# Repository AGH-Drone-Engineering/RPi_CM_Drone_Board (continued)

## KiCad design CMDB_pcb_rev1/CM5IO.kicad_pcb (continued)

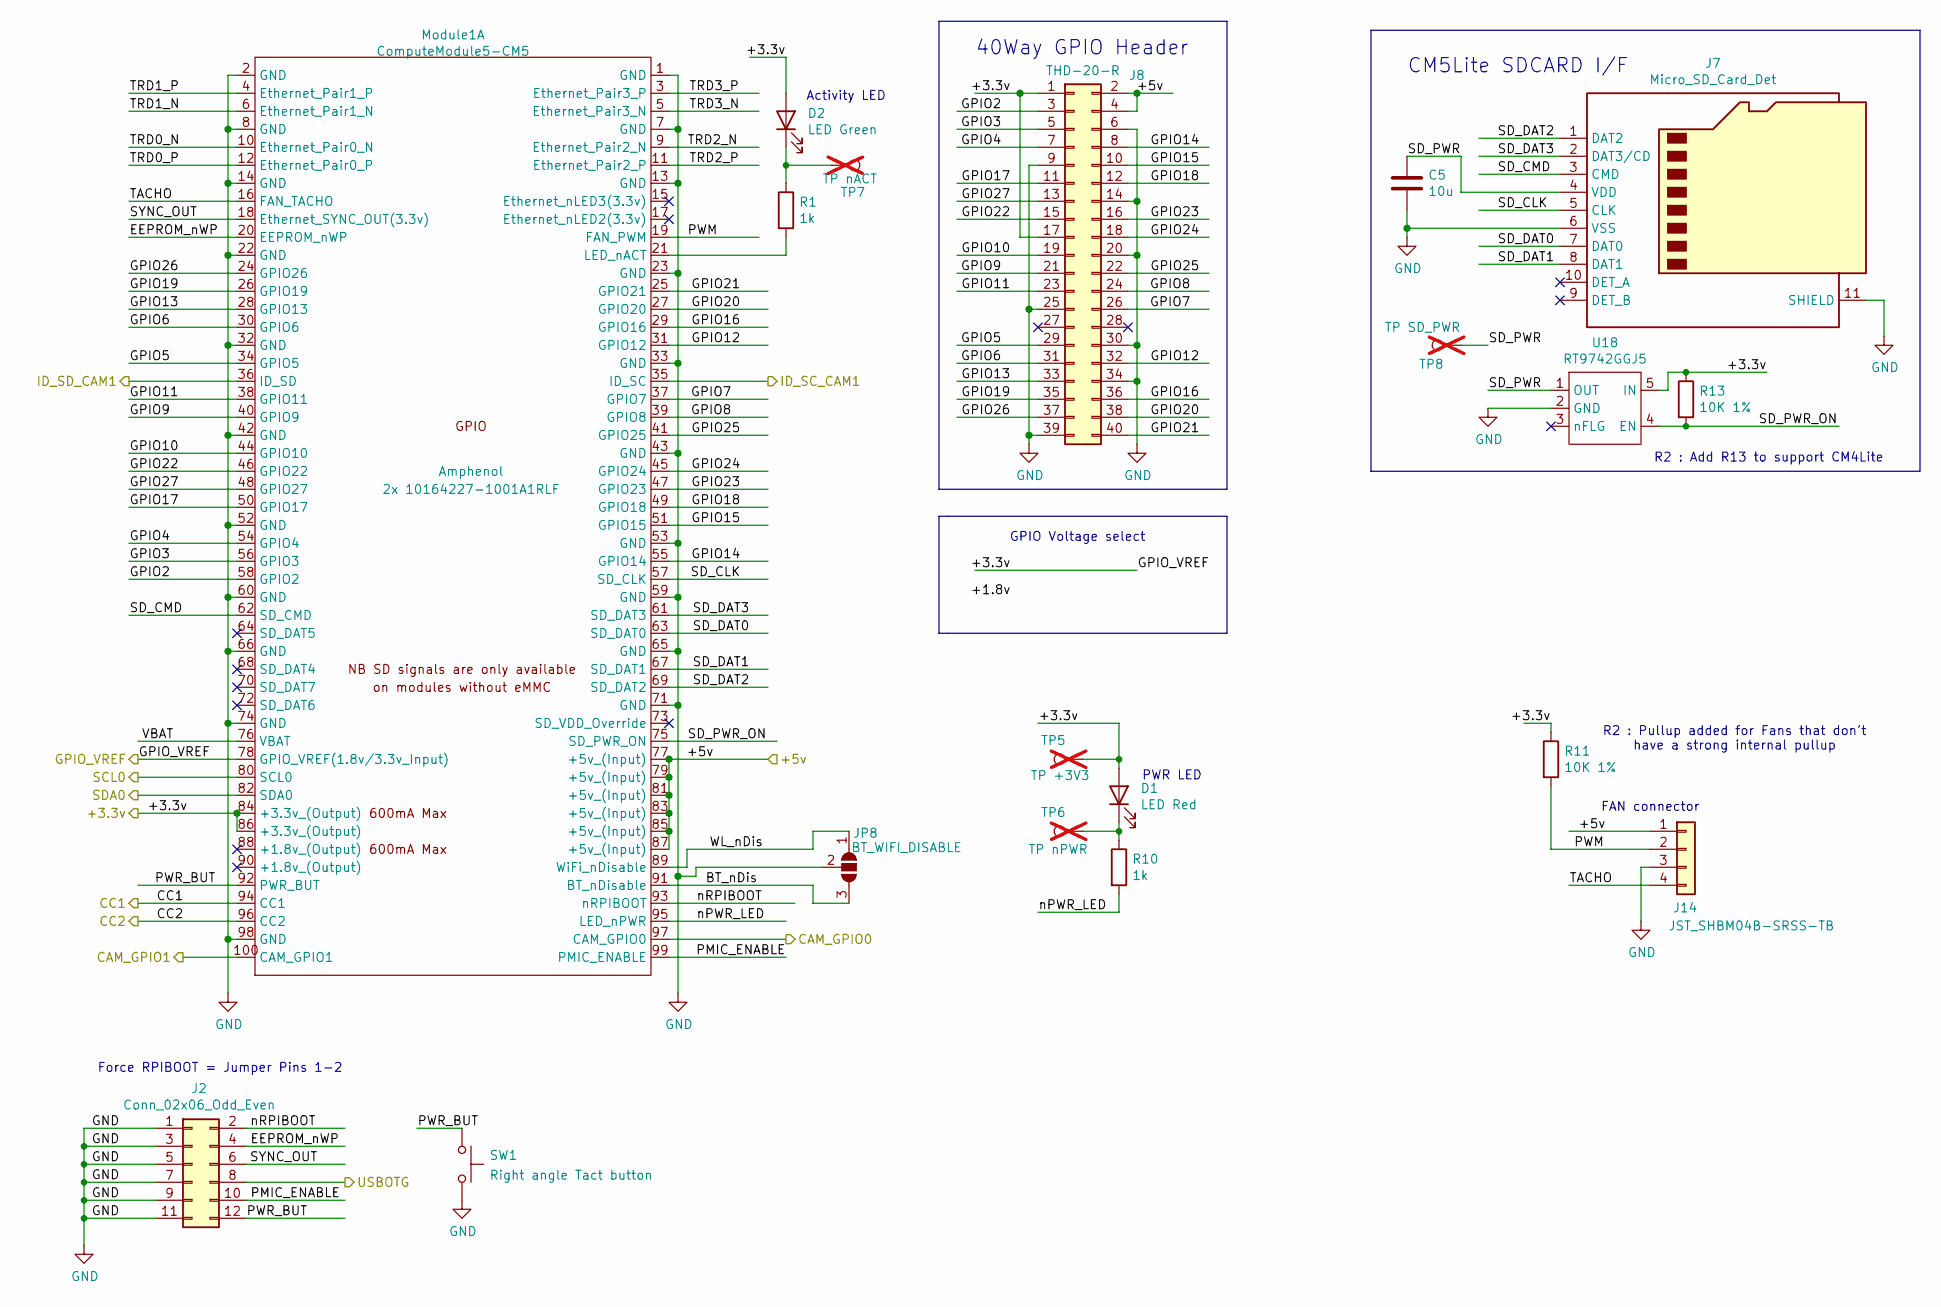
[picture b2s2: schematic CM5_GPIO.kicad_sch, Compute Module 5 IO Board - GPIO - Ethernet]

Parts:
C5: 10u; C_0805_2012Metric; Part Description 10uF 10% 10V Ceramic Capacitor X7R 0805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
D1: LED Red; LED_0603_1608Metric; Part Description Red 620nm LED Indication - Discrete 2.2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
D2: LED Green; LED_0603_1608Metric; Part Description Green 572nm LED Indication - Discrete 2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
J2: Conn_02x06_Odd_Even; PinHeader_2x06_P2.00mm_Vertical; Part Description PinHeader_2x06_P2.54mm_Vertical
J7: Micro_SD_Card_Det; SDCARD_MOLEX_503398-1892; Part Description 9 (8 + 1) Position Card Connector micro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
J8: THD-20-R; PinHeader_2x20_P2.54mm_Vertical; Part Description PinHeader_2x20_P2.54mm_Vertical
J14: JST_SHBM04B-SRSS-TB; JST_SH_BM04B-SRSS-TB_1x04-1MP_P1.00mm_Vertical; Part Description 4 pin vertical 1mm pitch connector
JP8: BT_WIFI_DISABLE; SolderJumper-3_P2.0mm_Open_TrianglePad1.0x1.5mm
Module1: ComputeModule5-CM5; Raspberry-Pi-5-Compute-Module; Part Description 100 Position Connector Receptacle, Cent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
R1, R10: 1k; R_0402_1005Metric; Part Description Resistor 1K M1005 1% 63mW
R11, R13: 10K 1%; R_0402_1005Metric; Part Description Resistor 10K M1005 1% 63mW
SW1: Right angle Tact button; SW_Push_1P1T_NO_CK_KMR2
TP5: TP +3V3; TestPoint_Pad_2.0x2.0mm; Part Description Test point; not fitted
TP6: TP nPWR; TestPoint_Pad_2.0x2.0mm; Part Description Test point; not fitted
TP7: TP nACT; TestPoint_Pad_2.0x2.0mm; Part Description Test point; not fitted
TP8: TP SD_PWR; TestPoint_Pad_2.0x2.0mm; Part Description Test point; not fitted
U18: RT9742GGJ5; SOT-23-5; Part Description Power Switch/Driver 1:1 N-Channel 1A TS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

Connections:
/+3.3v: D1.2 (A), D2.2 (A), J8.1, J8.17, Module1.78 (GPIO_VREF(1.8v/3.3v_Input)), Module1.84 (+3.3v_(Output)), Module1.86 (+3.3v_(Output)), R11.1, R13.1, TP5.1, U18.5 (IN); also elsewhere on the board
/+5v: J8.2, J8.4, J14.1, Module1.77 (+5v_(Input)), Module1.79 (+5v_(Input)), Module1.81 (+5v_(Input)), Module1.83 (+5v_(Input)), Module1.85 (+5v_(Input)), Module1.87 (+5v_(Input)); also elsewhere on the board
/CC1: Module1.94 (CC1); also elsewhere on the board
/CC2: Module1.96 (CC2); also elsewhere on the board
/CM5_GPIO ( Ethernet, GPIO, SDCARD)/BT_nDis: JP8.3 (B), Module1.91 (BT_nDisable)
/CM5_GPIO ( Ethernet, GPIO, SDCARD)/CAM_GPIO0: Module1.97 (CAM_GPIO0); also elsewhere on the board
/CM5_GPIO ( Ethernet, GPIO, SDCARD)/CAM_GPIO1: Module1.100 (CAM_GPIO1); also elsewhere on the board
/CM5_GPIO ( Ethernet, GPIO, SDCARD)/EEPROM_nWP: J2.4, Module1.20 (EEPROM_nWP)
/CM5_GPIO ( Ethernet, GPIO, SDCARD)/GPIO2: J8.3, Module1.58 (GPIO2)
/CM5_GPIO ( Ethernet, GPIO, SDCARD)/GPIO3: J8.5, Module1.56 (GPIO3)
/CM5_GPIO ( Ethernet, GPIO, SDCARD)/GPIO4: J8.7, Module1.54 (GPIO4)
/CM5_GPIO ( Ethernet, GPIO, SDCARD)/GPIO5: J8.29, Module1.34 (GPIO5)
/CM5_GPIO ( Ethernet, GPIO, SDCARD)/GPIO6: J8.31, Module1.30 (GPIO6)
/CM5_GPIO ( Ethernet, GPIO, SDCARD)/GPIO7: J8.26, Module1.37 (GPIO7)
/CM5_GPIO ( Ethernet, GPIO, SDCARD)/GPIO8: J8.24, Module1.39 (GPIO8)
/CM5_GPIO ( Ethernet, GPIO, SDCARD)/GPIO9: J8.21, Module1.40 (GPIO9)
/CM5_GPIO ( Ethernet, GPIO, SDCARD)/GPIO10: J8.19, Module1.44 (GPIO10)
/CM5_GPIO ( Ethernet, GPIO, SDCARD)/GPIO11: J8.23, Module1.38 (GPIO11)
/CM5_GPIO ( Ethernet, GPIO, SDCARD)/GPIO12: J8.32, Module1.31 (GPIO12)
/CM5_GPIO ( Ethernet, GPIO, SDCARD)/GPIO13: J8.33, Module1.28 (GPIO13)
/CM5_GPIO ( Ethernet, GPIO, SDCARD)/GPIO14: J8.8, Module1.55 (GPIO14)
/CM5_GPIO ( Ethernet, GPIO, SDCARD)/GPIO15: J8.10, Module1.51 (GPIO15)
/CM5_GPIO ( Ethernet, GPIO, SDCARD)/GPIO16: J8.36, Module1.29 (GPIO16)
/CM5_GPIO ( Ethernet, GPIO, SDCARD)/GPIO17: J8.11, Module1.50 (GPIO17)
/CM5_GPIO ( Ethernet, GPIO, SDCARD)/GPIO18: J8.12, Module1.49 (GPIO18)
/CM5_GPIO ( Ethernet, GPIO, SDCARD)/GPIO19: J8.35, Module1.26 (GPIO19)
/CM5_GPIO ( Ethernet, GPIO, SDCARD)/GPIO20: J8.38, Module1.27 (GPIO20)
/CM5_GPIO ( Ethernet, GPIO, SDCARD)/GPIO21: J8.40, Module1.25 (GPIO21)
/CM5_GPIO ( Ethernet, GPIO, SDCARD)/GPIO22: J8.15, Module1.46 (GPIO22)
/CM5_GPIO ( Ethernet, GPIO, SDCARD)/GPIO23: J8.16, Module1.47 (GPIO23)
/CM5_GPIO ( Ethernet, GPIO, SDCARD)/GPIO24: J8.18, Module1.45 (GPIO24)
/CM5_GPIO ( Ethernet, GPIO, SDCARD)/GPIO25: J8.22, Module1.41 (GPIO25)
/CM5_GPIO ( Ethernet, GPIO, SDCARD)/GPIO26: J8.37, Module1.24 (GPIO26)
/CM5_GPIO ( Ethernet, GPIO, SDCARD)/GPIO27: J8.13, Module1.48 (GPIO27)
/CM5_GPIO ( Ethernet, GPIO, SDCARD)/PMIC_ENABLE: J2.10, Module1.99 (PMIC_ENABLE)
/CM5_GPIO ( Ethernet, GPIO, SDCARD)/PWM: J14.2, Module1.19 (FAN_PWM), R11.2
/CM5_GPIO ( Ethernet, GPIO, SDCARD)/PWR_BUT: J2.12, Module1.92 (PWR_BUT), SW1.1
/CM5_GPIO ( Ethernet, GPIO, SDCARD)/SD_CLK: J7.5 (CLK), Module1.57 (SD_CLK)
/CM5_GPIO ( Ethernet, GPIO, SDCARD)/SD_CMD: J7.3 (CMD), Module1.62 (SD_CMD)
/CM5_GPIO ( Ethernet, GPIO, SDCARD)/SD_DAT0: J7.7 (DAT0), Module1.63 (SD_DAT0)
/CM5_GPIO ( Ethernet, GPIO, SDCARD)/SD_DAT1: J7.8 (DAT1), Module1.67 (SD_DAT1)
/CM5_GPIO ( Ethernet, GPIO, SDCARD)/SD_DAT2: J7.1 (DAT2), Module1.69 (SD_DAT2)
/CM5_GPIO ( Ethernet, GPIO, SDCARD)/SD_DAT3: J7.2 (DAT3/CD), Module1.61 (SD_DAT3)
/CM5_GPIO ( Ethernet, GPIO, SDCARD)/SD_PWR: C5.1, J7.4 (VDD), TP8.1, U18.1 (OUT)
/CM5_GPIO ( Ethernet, GPIO, SDCARD)/SD_PWR_ON: Module1.75 (SD_PWR_ON), R13.2, U18.4 (EN)
/CM5_GPIO ( Ethernet, GPIO, SDCARD)/SYNC_OUT: J2.6, Module1.18 (Ethernet_SYNC_OUT(3.3v))
/CM5_GPIO ( Ethernet, GPIO, SDCARD)/TACHO: J14.4, Module1.16 (FAN_TACHO)
/CM5_GPIO ( Ethernet, GPIO, SDCARD)/TRD0_N: Module1.10 (Ethernet_Pair0_N)
/CM5_GPIO ( Ethernet, GPIO, SDCARD)/TRD0_P: Module1.12 (Ethernet_Pair0_P)
/CM5_GPIO ( Ethernet, GPIO, SDCARD)/TRD1_N: Module1.6 (Ethernet_Pair1_N)
/CM5_GPIO ( Ethernet, GPIO, SDCARD)/TRD1_P: Module1.4 (Ethernet_Pair1_P)
/CM5_GPIO ( Ethernet, GPIO, SDCARD)/TRD2_N: Module1.9 (Ethernet_Pair2_N)
/CM5_GPIO ( Ethernet, GPIO, SDCARD)/TRD2_P: Module1.11 (Ethernet_Pair2_P)
/CM5_GPIO ( Ethernet, GPIO, SDCARD)/TRD3_N: Module1.5 (Ethernet_Pair3_N)
/CM5_GPIO ( Ethernet, GPIO, SDCARD)/TRD3_P: Module1.3 (Ethernet_Pair3_P)
/CM5_GPIO ( Ethernet, GPIO, SDCARD)/USBOTG: J2.8; also elsewhere on the board
/CM5_GPIO ( Ethernet, GPIO, SDCARD)/VBAT: Module1.76 (VBAT)
/CM5_GPIO ( Ethernet, GPIO, SDCARD)/WL_nDis: JP8.1 (A), Module1.89 (WiFi_nDisable)
/CM5_GPIO ( Ethernet, GPIO, SDCARD)/nPWR_LED: Module1.95 (LED_nPWR), R10.2
/CM5_GPIO ( Ethernet, GPIO, SDCARD)/nRPIBOOT: J2.2, Module1.93 (nRPIBOOT)
/CM5_HighSpeed/SCL0: Module1.80 (SCL0); also elsewhere on the board
/CM5_HighSpeed/SCL1: Module1.35 (ID_SC); also elsewhere on the board
/CM5_HighSpeed/SDA0: Module1.82 (SDA0); also elsewhere on the board
/CM5_HighSpeed/SDA1: Module1.36 (ID_SD); also elsewhere on the board
GND: C5.2, J2.1, J2.3, J2.5, J2.7, J2.9, J2.11, J7.6 (VSS), J7.11 (SHIELD), J8.6, J8.9, J8.14, J8.20, J8.25, J8.30, J8.34, J8.39, J14.3, JP8.2 (C), Module1.1 (GND), Module1.2 (GND), Module1.7 (GND), Module1.8 (GND), Module1.13 (GND), Module1.14 (GND), Module1.22 (GND), Module1.23 (GND), Module1.32 (GND), Module1.33 (GND), Module1.42 (GND), Module1.43 (GND), Module1.52 (GND), Module1.53 (GND), Module1.59 (GND), Module1.60 (GND), Module1.65 (GND), Module1.66 (GND), Module1.71 (GND), Module1.74 (GND), Module1.98 (GND), SW1.2, U18.2 (GND); also elsewhere on the board
unnamed: D1.1 (K), R10.1, TP6.1
unnamed: D2.1 (K), R1.1, TP7.1
unnamed: Module1.21 (LED_nACT), R1.2

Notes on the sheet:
40Way GPIO Header
R2 : Pullup added for Fans that don't have a strong internal pullup
Activity LED
R2 : Add R13 to support CM4Lite
GPIO Voltage select
Force RPIBOOT = Jumper Pins 1-2
PWR LED
FAN connector
CM5Lite SDCARD I/F

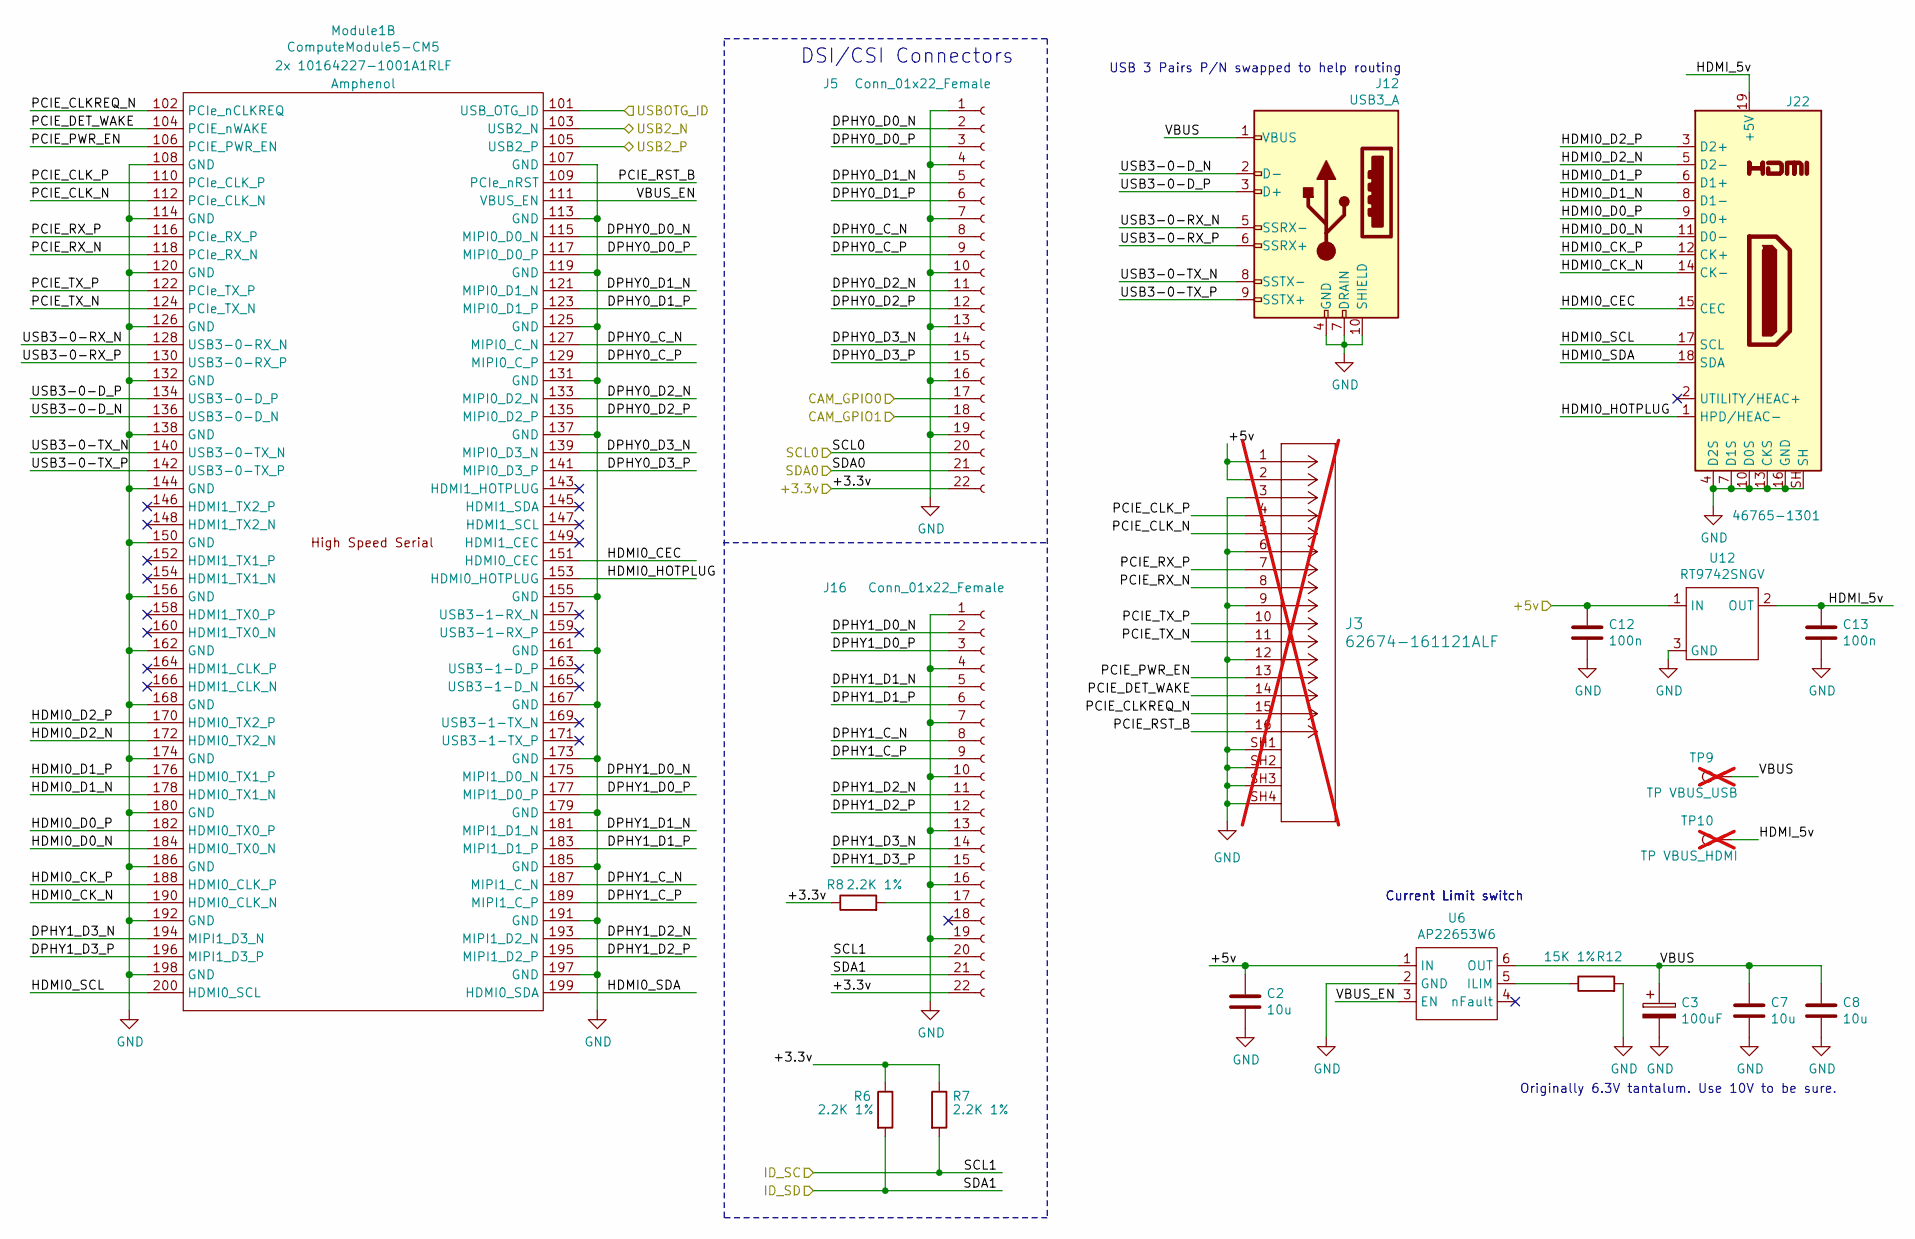
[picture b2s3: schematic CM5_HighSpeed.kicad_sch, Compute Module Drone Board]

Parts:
C2, C7, C8: 10u; C_0805_2012Metric; Part Description 10uF 10% 10V Ceramic Capacitor X7R 0805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
C3: 100uF; CP_EIA-7343-31_Kemet-D; Part Description Capacitor, SP-Cap, 100u, 6.3V, 15mR ESR
C12, C13: 100n; C_0402_1005Metric; Part Description 0.1uF 10% 16V Ceramic Capacitor X7R 040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
J3: 62674-161121ALF; CON16_1X16_DUT_58XF_GLE; not fitted
J5, J16: Conn_01x22_Female; Hirose_FH12-22S-0.5SH_1x22-1MP_P0.50mm_Horizontal; Part Description 22 Position FFC, FPC Connector Contacts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
J12: USB3_A; USB3_A_Molex_48393-001; Part Description USB 3.0 A connector
J22: 46765-1301; CONN_467651301_MOL; Part Description 0.40mm Pitch Micro HDMI Connector, Righ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
Module1: ComputeModule5-CM5; Raspberry-Pi-5-Compute-Module; Part Description 100 Position Connector Receptacle, Cent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
R6, R7, R8: 2.2K 1%; R_0402_1005Metric; Part Description Resistor 2.2K M1005 1% 63mW
R12: 15K 1%; R_0402_1005Metric; Part Description Resistor 15K M1005 1% 63mW
TP9: TP VBUS_USB; TestPoint_Pad_2.0x2.0mm; Part Description Test point; not fitted
TP10: TP VBUS_HDMI; TestPoint_Pad_2.0x2.0mm; Part Description Test point; not fitted
U6: AP22653W6; SOT-23-6; Part Description Power Switch/Driver 1:1 P-Channel 2.1A 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
U12: RT9742SNGV; TSOT-23_HandSoldering; Part Description Power Switch/Driver 1:1 N-Channel 500mA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

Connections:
/+3.3v: J5.22, J16.22, R6.1, R7.1, R8.1; also elsewhere on the board
/+5v: C2.1, C12.1, J3.1, J3.2, U6.1 (IN), U12.1 (IN); also elsewhere on the board
/CM5_GPIO ( Ethernet, GPIO, SDCARD)/CAM_GPIO0: J5.17; also elsewhere on the board
/CM5_GPIO ( Ethernet, GPIO, SDCARD)/CAM_GPIO1: J5.18; also elsewhere on the board
/CM5_GPIO ( Ethernet, GPIO, SDCARD)/USBOTG: Module1.101 (USB_OTG_ID); also elsewhere on the board
/CM5_HighSpeed/DPHY0_C_N: J5.8, Module1.127 (MIPI0_C_N)
/CM5_HighSpeed/DPHY0_C_P: J5.9, Module1.129 (MIPI0_C_P)
/CM5_HighSpeed/DPHY0_D0_N: J5.2, Module1.115 (MIPI0_D0_N)
/CM5_HighSpeed/DPHY0_D0_P: J5.3, Module1.117 (MIPI0_D0_P)
/CM5_HighSpeed/DPHY0_D1_N: J5.5, Module1.121 (MIPI0_D1_N)
/CM5_HighSpeed/DPHY0_D1_P: J5.6, Module1.123 (MIPI0_D1_P)
/CM5_HighSpeed/DPHY0_D2_N: J5.11, Module1.133 (MIPI0_D2_N)
/CM5_HighSpeed/DPHY0_D2_P: J5.12, Module1.135 (MIPI0_D2_P)
/CM5_HighSpeed/DPHY0_D3_N: J5.14, Module1.139 (MIPI0_D3_N)
/CM5_HighSpeed/DPHY0_D3_P: J5.15, Module1.141 (MIPI0_D3_P)
/CM5_HighSpeed/DPHY1_C_N: J16.8, Module1.187 (MIPI1_C_N)
/CM5_HighSpeed/DPHY1_C_P: J16.9, Module1.189 (MIPI1_C_P)
/CM5_HighSpeed/DPHY1_D0_N: J16.2, Module1.175 (MIPI1_D0_N)
/CM5_HighSpeed/DPHY1_D0_P: J16.3, Module1.177 (MIPI1_D0_P)
/CM5_HighSpeed/DPHY1_D1_N: J16.5, Module1.181 (MIPI1_D1_N)
/CM5_HighSpeed/DPHY1_D1_P: J16.6, Module1.183 (MIPI1_D1_P)
/CM5_HighSpeed/DPHY1_D2_N: J16.11, Module1.193 (MIPI1_D2_N)
/CM5_HighSpeed/DPHY1_D2_P: J16.12, Module1.195 (MIPI1_D2_P)
/CM5_HighSpeed/DPHY1_D3_N: J16.14, Module1.194 (MIPI1_D3_N)
/CM5_HighSpeed/DPHY1_D3_P: J16.15, Module1.196 (MIPI1_D3_P)
/CM5_HighSpeed/HDMI0_CEC: J22.15 (CEC), Module1.151 (HDMI0_CEC)
/CM5_HighSpeed/HDMI0_CK_N: J22.14 (CK-), Module1.190 (HDMI0_CLK_N)
/CM5_HighSpeed/HDMI0_CK_P: J22.12 (CK+), Module1.188 (HDMI0_CLK_P)
/CM5_HighSpeed/HDMI0_D0_N: J22.11 (D0-), Module1.184 (HDMI0_TX0_N)
/CM5_HighSpeed/HDMI0_D0_P: J22.9 (D0+), Module1.182 (HDMI0_TX0_P)
/CM5_HighSpeed/HDMI0_D1_N: J22.8 (D1-), Module1.178 (HDMI0_TX1_N)
/CM5_HighSpeed/HDMI0_D1_P: J22.6 (D1+), Module1.176 (HDMI0_TX1_P)
/CM5_HighSpeed/HDMI0_D2_N: J22.5 (D2-), Module1.172 (HDMI0_TX2_N)
/CM5_HighSpeed/HDMI0_D2_P: J22.3 (D2+), Module1.170 (HDMI0_TX2_P)
/CM5_HighSpeed/HDMI0_HOTPLUG: J22.1 (HPD/HEAC-), Module1.153 (HDMI0_HOTPLUG)
/CM5_HighSpeed/HDMI0_SCL: J22.17 (SCL), Module1.200 (HDMI0_SCL)
/CM5_HighSpeed/HDMI0_SDA: J22.18 (SDA), Module1.199 (HDMI0_SDA)
/CM5_HighSpeed/HDMI_5v: C13.1, J22.19 (+5V), TP10.1, U12.2 (OUT)
/CM5_HighSpeed/PCIE_CLKREQ_N: J3.15, Module1.102 (PCIe_nCLKREQ)
/CM5_HighSpeed/PCIE_CLK_N: J3.5, Module1.112 (PCIe_CLK_N)
/CM5_HighSpeed/PCIE_CLK_P: J3.4, Module1.110 (PCIe_CLK_P)
/CM5_HighSpeed/PCIE_DET_WAKE: J3.14, Module1.104 (PCIE_nWAKE)
/CM5_HighSpeed/PCIE_PWR_EN: J3.13, Module1.106 (PCIE_PWR_EN)
/CM5_HighSpeed/PCIE_RST_B: J3.16, Module1.109 (PCIe_nRST)
/CM5_HighSpeed/PCIE_RX_N: J3.8, Module1.118 (PCIe_RX_N)
/CM5_HighSpeed/PCIE_RX_P: J3.7, Module1.116 (PCIe_RX_P)
/CM5_HighSpeed/PCIE_TX_N: J3.11, Module1.124 (PCIe_TX_N)
/CM5_HighSpeed/PCIE_TX_P: J3.10, Module1.122 (PCIe_TX_P)
/CM5_HighSpeed/SCL0: J5.20; also elsewhere on the board
/CM5_HighSpeed/SCL1: J16.20, R7.2; also elsewhere on the board
/CM5_HighSpeed/SDA0: J5.21; also elsewhere on the board
/CM5_HighSpeed/SDA1: J16.21, R6.2; also elsewhere on the board
/CM5_HighSpeed/USB3-0-D_N: J12.2 (D-), Module1.136 (USB3-0-D_N)
/CM5_HighSpeed/USB3-0-D_P: J12.3 (D+), Module1.134 (USB3-0-D_P)
/CM5_HighSpeed/USB3-0-RX_N: J12.5 (SSRX-), Module1.128 (USB3-0-RX_N)
/CM5_HighSpeed/USB3-0-RX_P: J12.6 (SSRX+), Module1.130 (USB3-0-RX_P)
/CM5_HighSpeed/USB3-0-TX_N: J12.8 (SSTX-), Module1.140 (USB3-0-TX_N)
/CM5_HighSpeed/USB3-0-TX_P: J12.9 (SSTX+), Module1.142 (USB3-0-TX_P)
/CM5_HighSpeed/VBUS: C3.1, C7.1, C8.1, J12.1 (VBUS), TP9.1, U6.6 (OUT)
/CM5_HighSpeed/VBUS_EN: Module1.111 (VBUS_EN), U6.3 (EN)
/USB2_N: Module1.103 (USB2_N); also elsewhere on the board
/USB2_P: Module1.105 (USB2_P); also elsewhere on the board
GND: C2.2, C3.2, C7.2, C8.2, C12.2, C13.2, J3.3, J3.6, J3.9, J3.12, J3.SH1, J3.SH2, J3.SH3, J3.SH4, J5.1, J5.4, J5.7, J5.10, J5.13, J5.16, J5.19, J12.4 (GND), J12.7 (DRAIN), J12.10 (SHIELD), J16.1, J16.4, J16.7, J16.10, J16.13, J16.16, J16.19, J22.4 (D2S), J22.7 (D1S), J22.10 (D0S), J22.13 (CKS), J22.16 (GND), J22.SH, Module1.107 (GND), Module1.108 (GND), Module1.113 (GND), Module1.114 (GND), Module1.119 (GND), Module1.120 (GND), Module1.125 (GND), Module1.126 (GND), Module1.131 (GND), Module1.132 (GND), Module1.137 (GND), Module1.138 (GND), Module1.144 (GND), Module1.150 (GND), Module1.155 (GND), Module1.156 (GND), Module1.161 (GND), Module1.162 (GND), Module1.167 (GND), Module1.168 (GND), Module1.173 (GND), Module1.174 (GND), Module1.179 (GND), Module1.180 (GND), Module1.185 (GND), Module1.186 (GND), Module1.191 (GND), Module1.192 (GND), Module1.197 (GND), Module1.198 (GND), R12.2, U6.2 (GND), U12.3 (GND); also elsewhere on the board
unnamed: J16.17, R8.2
unnamed: R12.1, U6.5 (ILIM)

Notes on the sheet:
USB 3 Pairs P/N swapped to help routing
Current Limit switch
DSI/CSI Connectors
Originally 6.3V tantalum. Use 10V to be sure.

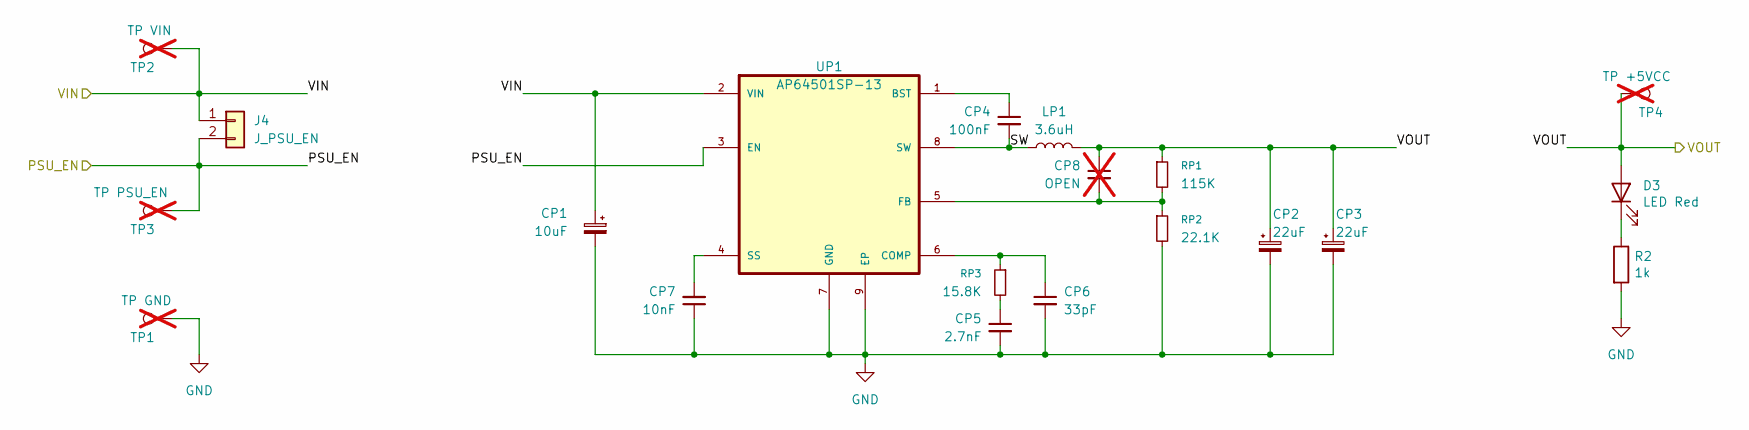
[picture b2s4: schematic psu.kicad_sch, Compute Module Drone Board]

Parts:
CP1: 10uF; CP_EIA-6032-28_Kemet-C_HandSolder
CP2, CP3: 22uF; CP_EIA-3528-21_Kemet-B_HandSolder
CP4: 100nF; C_0805_2012Metric_Pad1.18x1.45mm_HandSolder
CP5: 2.7nF; C_0805_2012Metric_Pad1.18x1.45mm_HandSolder
CP6: 33pF; C_0805_2012Metric_Pad1.18x1.45mm_HandSolder
CP7: 10nF; C_0805_2012Metric_Pad1.18x1.45mm_HandSolder
CP8: OPEN; C_0805_2012Metric_Pad1.18x1.45mm_HandSolder; not fitted
D3: LED Red; LED_0603_1608Metric; Part Description Red 620nm LED Indication - Discrete 2.2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
J4: J_PSU_EN; PinHeader_1x02_P2.54mm_Vertical
LP1: 3.6uH; L_Bourns-SRN8040_8x8.15mm
R2: 1k; R_0402_1005Metric; Part Description Resistor 1K M1005 1% 63mW
RP1: 115K; R_0805_2012Metric_Pad1.20x1.40mm_HandSolder
RP2: 22.1K; R_0805_2012Metric_Pad1.20x1.40mm_HandSolder
RP3: 15.8K; R_0805_2012Metric_Pad1.20x1.40mm_HandSolder
TP1: TP GND; TestPoint_Pad_2.0x2.0mm; Part Description Test point; not fitted
TP2: TP VIN; TestPoint_Pad_2.0x2.0mm; Part Description Test point; not fitted
TP3: TP PSU_EN; TestPoint_Pad_2.0x2.0mm; Part Description Test point; not fitted
TP4: TP +5VCC; TestPoint_Pad_2.0x2.0mm; Part Description Test point; not fitted
UP1: AP64501SP-13; SOP_AP64501SP-13_DIO

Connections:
/+5v: CP2.1, CP3.1, CP8.1, D3.2 (A), LP1.2, RP1.1, TP4.1; also elsewhere on the board
/PSU/PSU_EN: J4.2, TP3.1, UP1.3 (EN)
/PSU/SW: CP4.2, LP1.1, UP1.8 (SW)
/VIN: CP1.1, J4.1, TP2.1, UP1.2 (VIN); also elsewhere on the board
GND: CP1.2, CP2.2, CP3.2, CP5.2, CP6.2, CP7.1, R2.2, RP2.2, TP1.1, UP1.7 (GND), UP1.9 (EP); also elsewhere on the board
unnamed: CP5.1, RP3.2
unnamed: D3.1 (K), R2.1
unnamed: CP4.1, UP1.1 (BST)
unnamed: CP6.1, RP3.1, UP1.6 (COMP)
unnamed: CP8.2, RP1.2, RP2.1, UP1.5 (FB)
unnamed: CP7.2, UP1.4 (SS)

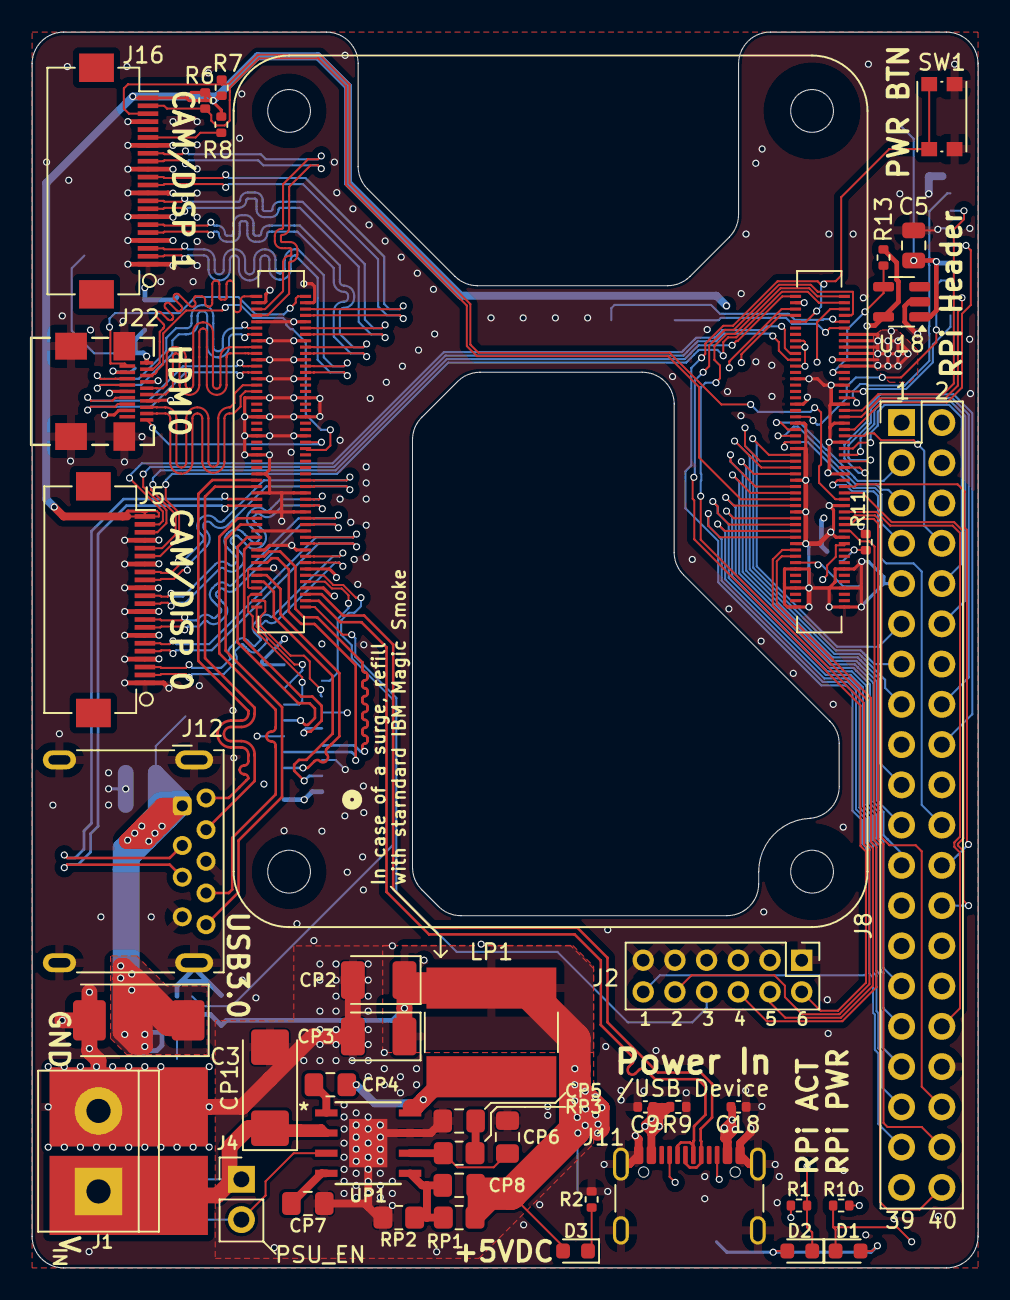
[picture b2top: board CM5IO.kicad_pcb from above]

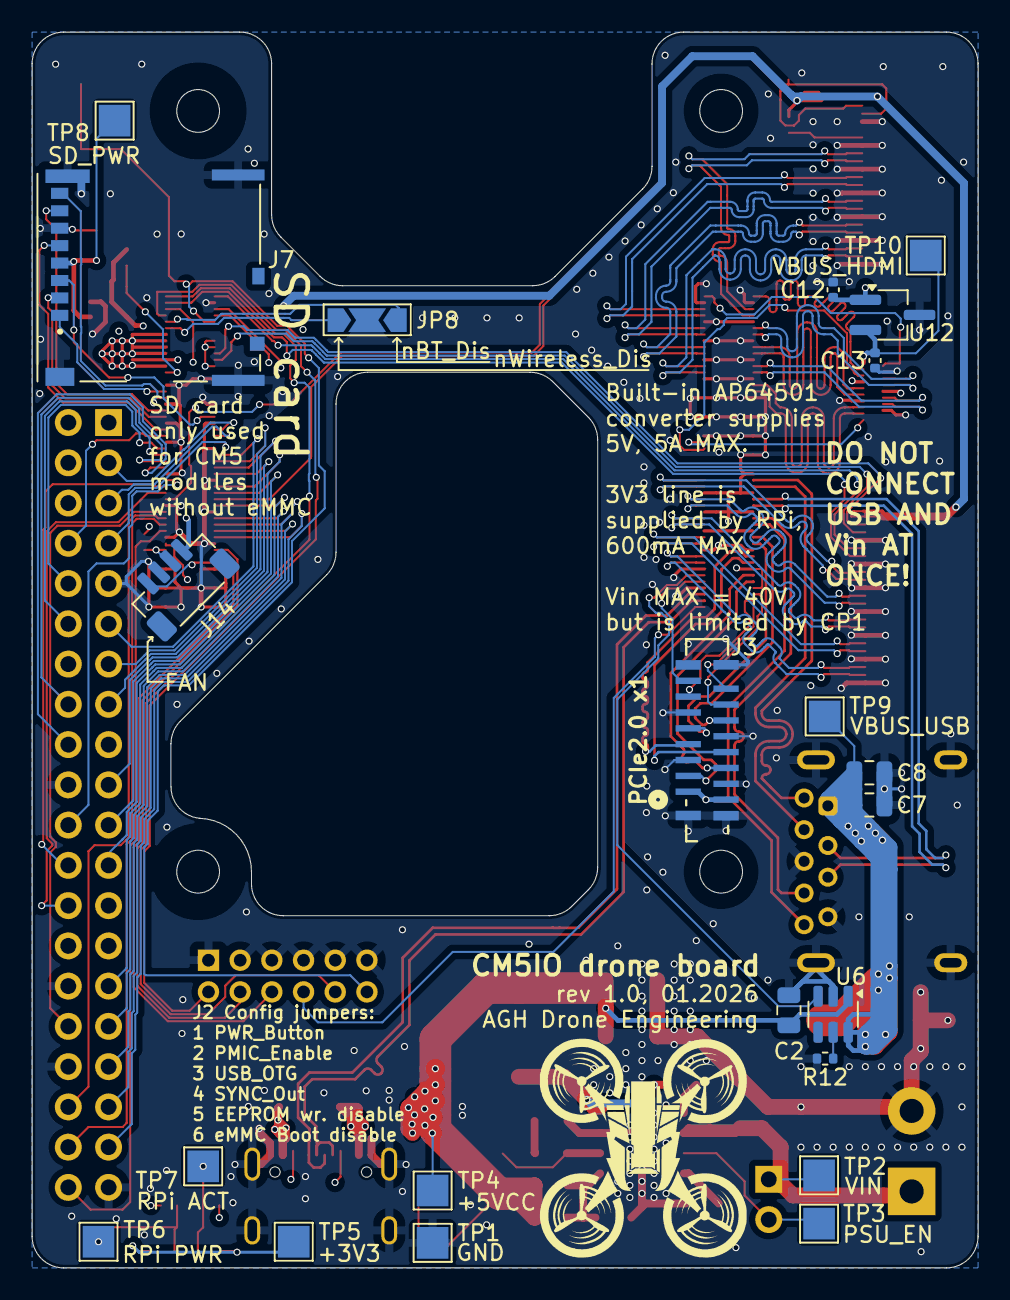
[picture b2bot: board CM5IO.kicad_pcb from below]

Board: 4 copper layers, 59.7 x 78.0 mm, 65 parts (22 on the bottom side), 123 nets.

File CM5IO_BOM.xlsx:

Qty/ board | Ref | Value | Footprint | Desc | Part No. | MOUSER |  | Farnell |  | TME
 |  |  |  |  |  | Unit Price | Code | Unit Price | Code | Unit Price | Code | min. Il. na 10 płytek
4 | C9,C12,C13,C18 | 100n | Capacitor_SMD:C_0402_1005Metric | 0.1uF 10% 16V Ceramic Capacitor X7R 0402 (1005 Metric) | - |  |  |  |  | 3.9190000000000003E-2 | 04025C104KAT2A | 42 | 1.6459800000000002
1 | CP6 | 33pF | Capacitor_SMD:C_0805_2012Metric_Pad1.18x1.45mm_HandSolder | - | - |  |  |  |  | 0.20480000000000001 | 08055A330KAT2A | 12 | 2.4576000000000002
1 | CP5 | 2.7nF | Capacitor_SMD:C_0805_2012Metric_Pad1.18x1.45mm_HandSolder | - | - |  |  |  |  | 0.18210000000000001 | 08055C272KAT2A | 12 | 2.1852
1 | CP7 | 10nF | Capacitor_SMD:C_0805_2012Metric_Pad1.18x1.45mm_HandSolder | - | - |  |  |  |  | 0.1421 | 08055C103KAT2A | 12 | 1.7052 | 10nF was not available. Soldered from private stash.
1 | CP4 | 100nF | Capacitor_SMD:C_0805_2012Metric_Pad1.18x1.45mm_HandSolder | - | - |  |  |  |  | 4.1669999999999999E-2 | 08055C104KAT2A | 12 | 0.50004000000000004
4 | C2,C5,C7,C8 | 10u | Capacitor_SMD:C_0805_2012Metric | 10uF 10% 10V Ceramic Capacitor X7R 0805 (2012 Metric) | - |  |  |  |  | 0.28220000000000001 | 08055C105KAT2A | 42 | 11.852399999999999 | Here also is a mistake - should be 10uF, is 1uF. Soldered from private stash.
3 | R1,R2,R10 | 1k | Resistor_SMD:R_0402_1005Metric | Resistor 1K M1005 1% 63mW | - |  |  |  |  | 3.3119999999999997E-2 | SMD0402-1K-1% | 100 | 3.3119999999999998
4 | R6,R7,R8,R9 | 2.2K 1% | Resistor_SMD:R_0402_1005Metric | Resistor 2.2K M1005 1% 63mW | - |  |  |  |  | 3.9050000000000001E-2 | SMD0402-2K2-1% | 100 | 3.9050000000000002
2 | R11,R13 | 10K 1% | Resistor_SMD:R_0402_1005Metric | Resistor 10K M1005 1% 63mW | - |  |  |  |  | 1.7569999999999999E-2 | SMD0402-10K-1% | 100 | 1.7569999999999999
1 | R12 | 15K 1% | Resistor_SMD:R_0402_1005Metric | Resistor 15K M1005 1% 63mW | - |  |  |  |  | 3.6560000000000002E-2 | SMD0402-15K-1% | 100 | 3.6560000000000001
1 | RP1 | 115K | Resistor_SMD:R_0805_2012Metric_Pad1.20x1.40mm_HandSolder | - | - |  |  |  |  | 0.21560000000000001 | ERA6AEB1153V | 12 | 2.5872000000000002
1 | RP2 | 22.1K | Resistor_SMD:R_0805_2012Metric_Pad1.20x1.40mm_HandSolder | - | - |  |  |  |  | 5.9389999999999998E-2 | SMD0805-22K1-1% | 100 | 5.9390000000000001
1 | RP3 | 15.8K | Resistor_SMD:R_0805_2012Metric_Pad1.20x1.40mm_HandSolder | - | - |  |  |  |  | 6.7129999999999995E-2 | SMD0805-15.8K-1% | 100 | 6.7129999999999992
1 | J1 | POWER TERMINAL | TerminalBlock:TerminalBlock_bornier-2_P5.08mm | - | - |  |  |  |  |  | Will be unused |  | 0
1 | J2 | Conn_02x06_Odd_Even | Connector_PinHeader_2.00mm:PinHeader_2x06_P2.00mm_Vertical | PinHeader_2x06_P2.54mm_Vertical | - |  |  |  |  | 1.093 | ZL303-2X40P | 10 | 10.93
2 | J2 |  |  | Zwory do J2 |  |  |  |  |  | 0.29389999999999999 | JUMPER-2.0/B | 12 | 3.5267999999999997
1 | J4 | J_PSU_EN | Connector_PinHeader_2.54mm:PinHeader_1x02_P2.54mm_Vertical | - | - |  |  |  |  |  |  |  | 0
1 | J8 | THD-20-R | Connector_PinHeader_2.54mm:PinHeader_2x20_P2.54mm_Vertical | PinHeader_2x20_P2.54mm_Vertical | THD-20-R
 |  |  |  |  |  |  |  |  |  |  |  | SUMA | 62.67242000000001
1 | CP1 | 10uF | Capacitor_Tantalum_SMD:CP_EIA-3528-21_Kemet-C_HandSolder | Tantalum, Kemet-C, 10uF@35V min. | - |  |  |  |  | 3.7360000000000002 | TAJC106K035R
2 | CP2,CP3 | 22uF | Capacitor_Tantalum_SMD:CP_EIA-3528-21_Kemet-B_HandSolder | Tantalum, Kemet-B, 22uF@10V min. | - |  |  |  |  | 1.643 | TAJB226K016R
1 | C3 | 100uF | Capacitor_Tantalum_SMD:CP_EIA-7343-31_Kemet-D | Kemet-D, 10V | - |  |  |  |  | 2.2789999999999999 | TAJD106K035R | Mistake has been made here - this is 10uF instead of 100uF. Soldered anyway.
2 | D1,D3 | LED Red | LED_SMD:LED_0603_1608Metric | Red 620nm LED Indication - Discrete 2.2V 2-SMD, No Lead | SML-A12U8TT86Q | 0.38300000000000001 | 859-LTST-S270KRKT | 1.65 | 3434715 | 0 | -
1 | D2 | LED Green | LED_SMD:LED_0603_1608Metric | Green 572nm LED Indication - Discrete 2.2V 2-SMD, No Lead | SML-A12M8TT86N | 0.30499999999999999 | 859-LTST-S270KGKT | 1.64 | 3434712 | 0 | -
2 | J5,J16 | Conn_01x22_Female | CM5IO:Hirose_FH12-22S-0.5SH_1x22-1MP_P0.50mm_Horizontal | 22 Position FFC, FPC Connector Contacts, Bottom 0.020" (0.50mm) Surface Mount, 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 | FH12-22S-0.5SH55 | 5.68 | 798-FH12-22S-0.5SH55 | 7.17 | 2300373 | 0 | -
1 | J7 | Micro_SD_Card_Det | CM5IO:SDCARD_MOLEX_503398-1892 | 9 (8 + 1) Position Card Connector microSDâ„¢ Surface Mount, Right Angle Gold | 503398-1892 |  |  |  |  | 8.41 | MX-503398-1892 | Not necessary, if no SD card is used
1 | J11 | USB_C_Receptacle_USB2.0 | Connector_USB:USB_C_Receptacle_GCT_USB4105-xx-A_16P_TopMnt_Horizontal | USBC USB2 data and power connector | USBF31-0171 |  |  |  |  | 2.5059999999999998 | USB4105-GF-A-060 (substitute)
1 | J12 | USB3_A | Connector_USB:USB3_A_Molex_48393-001 | USB 3.0 A connector | 48393-0003 |  |  |  |  | 9.67 | MX-48393-0003
1 | J14 | JST_SHBM04B-SRSS-TB | Connector_JST:JST_SH_BM04B-SRSS-TB_1x04-1MP_P1.00mm_Vertical | 4 pin vertical 1mm pitch connector | SHBM04B-SRSS-TB |  |  |  |  | 1.4419999999999999 | SM04B-SRSS-TB
1 | J22 | 46765-1301 | CM5IO:CONN_467651301_MOL | 0.40mm Pitch Micro HDMI Connector, Right-Angle Receptacle, Surface Mount, with 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 | 46765-1301 | 7.7 | 538-46765-1301 | 8.82 | 2614867 | 0 | -
1 | LP1 | 3.6uH | Inductor_SMD:L_Bourns-SRN8040_8x8.15mm | - | SRN8040HA-3R6M | 1.7 | 652-SRN8040HA-3R6M | 2.52 | 4216300 | 0 | -
2 | Module1 | ComputeModule5-CM5 | CM5IO:Raspberry-Pi-5-Compute-Module | 100 Position Connector Receptacle, Center Strip Contacts Surface Mount Gold | 10164227-1001A1RLF | 5.5529999999999999 | DF40C-100DS-0.4V(51) (substitute) | 7.43 | 4137104 | 0 | -
1 | SW1 | Right angle Tact button | Button_Switch_SMD:SW_Push_1P1T_NO_CK_KMR2 | - | KMR221G LFS |  |  |  |  | 1.0469999999999999 | KMR221GLFS
1 | U6 | AP22653W6 | Package_TO_SOT_SMD:SOT-23-6 | Power Switch/Driver 1:1 P-Channel 2.1A SOT-23-6 | AP22653W6 |  |  |  |  | 1.45 | AP22653W6-7
1 | U12 | RT9742SNGV | Package_TO_SOT_SMD:TSOT-23_HandSoldering | Power Switch/Driver 1:1 N-Channel 500mA SOT-23-3 | RT9742SNGV | 1.04 | 835-RT9742SNGV | 1.5 | 2575555 | 0 | -
1 | U18 | RT9742GGJ5 | Package_TO_SOT_SMD:SOT-23-5 | Power Switch/Driver 1:1 N-Channel 1A TSOT-23-5 | RT9742GGJ5 | 1.19 | 835-RT9742GGJ5 | 0 | - | 0 | - | Not necessary, if no SD card is used
1 | UP1 | AP64501SP-13 | CM5IO:SOP_AP64501SP-13_DIO | - | AP64501SP-13 |  |  |  |  | 7.11 | AP64501SP-13
 |  |  |  |  |  | 35.166999999999994 | SUMA / płytka | 46.980000000000004 | SUMA / płytka | 40.936 | SUMA / płytka
